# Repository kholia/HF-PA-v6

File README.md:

### HF-PA-v6

RF "Lego" blocks.

The idea behind this work is to build radio-things (TM) in stages which
connect to each other.

Note: This `HF-PA-v6` is like https://github.com/kholia/HF-PA-v5 which has been
broken out in stages. This makes the designing, and debugging processes much
easier.

#### Results

October-2022 UPDATE: The PCB manufactured by JLCPCB was successfully validated.
We could get 5W+ with IRF510 @ 20v drain @ 28 MHz. Output at 14 MHz can be more
than 10W easily too.

PCB bug (in `HF-PA-Combined` version): Please cut the positive trace going
between C15 and JP2 to enable dynamic PA voltage control using PTT. This bug
is fixed in `HF-PA-Combined-v2` version for future production.

NOTE: See https://github.com/kholia/HF-PA-v6/tree/master/HF-PA-Combined for the
schematics, design files, and a PCB render screenshot.

IRF510 @ 14 MHz -> 20v @ drain. RF output > 7.5W. No LPF. Clean'ish looking
output. No oscillations. BS170 @ 5.5v. DC bias set high for max'ish "Idq".

IRF510 @ 21 MHz -> 15v @ drain. 12.75W DC input. RF output > 3W. No LPF.
Clean'ish looking output. No oscillations. BS170 @ 5.5v. DC bias set high for
max'ish "Idq". Almost 4W can be achieved with max "Idq".

IRF510 @ 28 MHz -> 14v @ drain. 9W DC input. RF output > 2W (on meter). No LPF.
Clean'ish looking output. No oscillations. BS170 @ 5.5v. DC bias set high for
max'ish "Idq".

IRF510 @ 28 MHz -> 17v @ drain. RF output > 2.25W (on scope), 3.5W on RF power
meter. No LPF. Clean'ish looking output. No oscillations. BS170 @ 6v. DC bias
set high for max "Idq" @ 4.2v roughly.

Note: We can even use 30v (and higher+) drain voltages (PA voltages) with
IRF510 - with much more care though!

Even 3W can get worldwide DX contacts when propagation is playing along ;)

7W (or less) of HF RF power offers global communications coverage when
propagation is good:

#### BOM Notes

See https://github.com/kholia/HF-PA-v5 for the BOM and BOM sources.

- https://github.com/kholia/HF-PA-v5#pa-bom

- https://github.com/kholia/HF-PA-v5#bom--equipment-sources

#### Build Notes

L1 can be a simple choke (FT37-43 25 turns of 27 to 29 SWG wire).

L2 needs to be a bifilar transformer on FT50-43 core (10 turns with 24/25/26
SWG wire).

#### Notes

[BS170 Driver Performance](./BS170-Driver-Performance.txt)

As Vds is increased, the Vgs needs to be increased too - see the following
graph.

If the gate DC bias is too less, the MOSFET will not turn on properly, and will
generate a lot of distortion - one prominent distorted waveform will be at
half-the-operating frequency!

When operating at max "Idq" (for best linearity), the power to the IRF510
should be PTT controlled - otherwise too much (battery) power will turn to heat
instead of RF!

#### Special Notes

While IRF510 can get destroyed due to oscillations, in my case it has been a
failed 7805 (or 78L05) regulator which ultimately causes cascading failures.

A 7805 regulator can fail in fail-short mode, where `Vout == Vin`! This changes
the bias of the driver stage (BS170), and it goes in full conduction
immediately without any RF input because Vgs(th) is exceeded quite easily.
This causes further failures in the PA system!

My 7805s (and 78L05s) of dubious origin were failing (Vout shorted to Vin!)
around 20v to 24v. Here is what `bd139` (from https://www.eevblog.com/forum/)
has to say on this topic,

```
None of the voltage regulators work properly above about 20V if you want 5V
out. If you need to drop more, add a preregulator.

I found this out the hard way as well dropping 28V to 5V DC for logic in an RF
PA driver. Currently waiting for a board spin. I only needed 50mA and didn't
want RF noise so I went with a simple MOSFET/zener/resistor preregulator to
drop it down to 18Vish. Because the current requirements are relatively low I
don't need to heatsink either then as the load is spread evenly across both
MOSFET and 7805.

Also if you value the circuit it's driving, stick a 5W 5.6V zener across the
regulator output. That will smoke the prereg / regulator not the load!
```

Thank you `bd139`!

#### PCB Renderings

#### Joining In

Are you interested in such projects, and spam-free technical discussions?

If yes, you might be interested in joining [the 'HAMBREWERS' Telegram group](https://t.me/+TwzGyKGe8_QI_B3y).

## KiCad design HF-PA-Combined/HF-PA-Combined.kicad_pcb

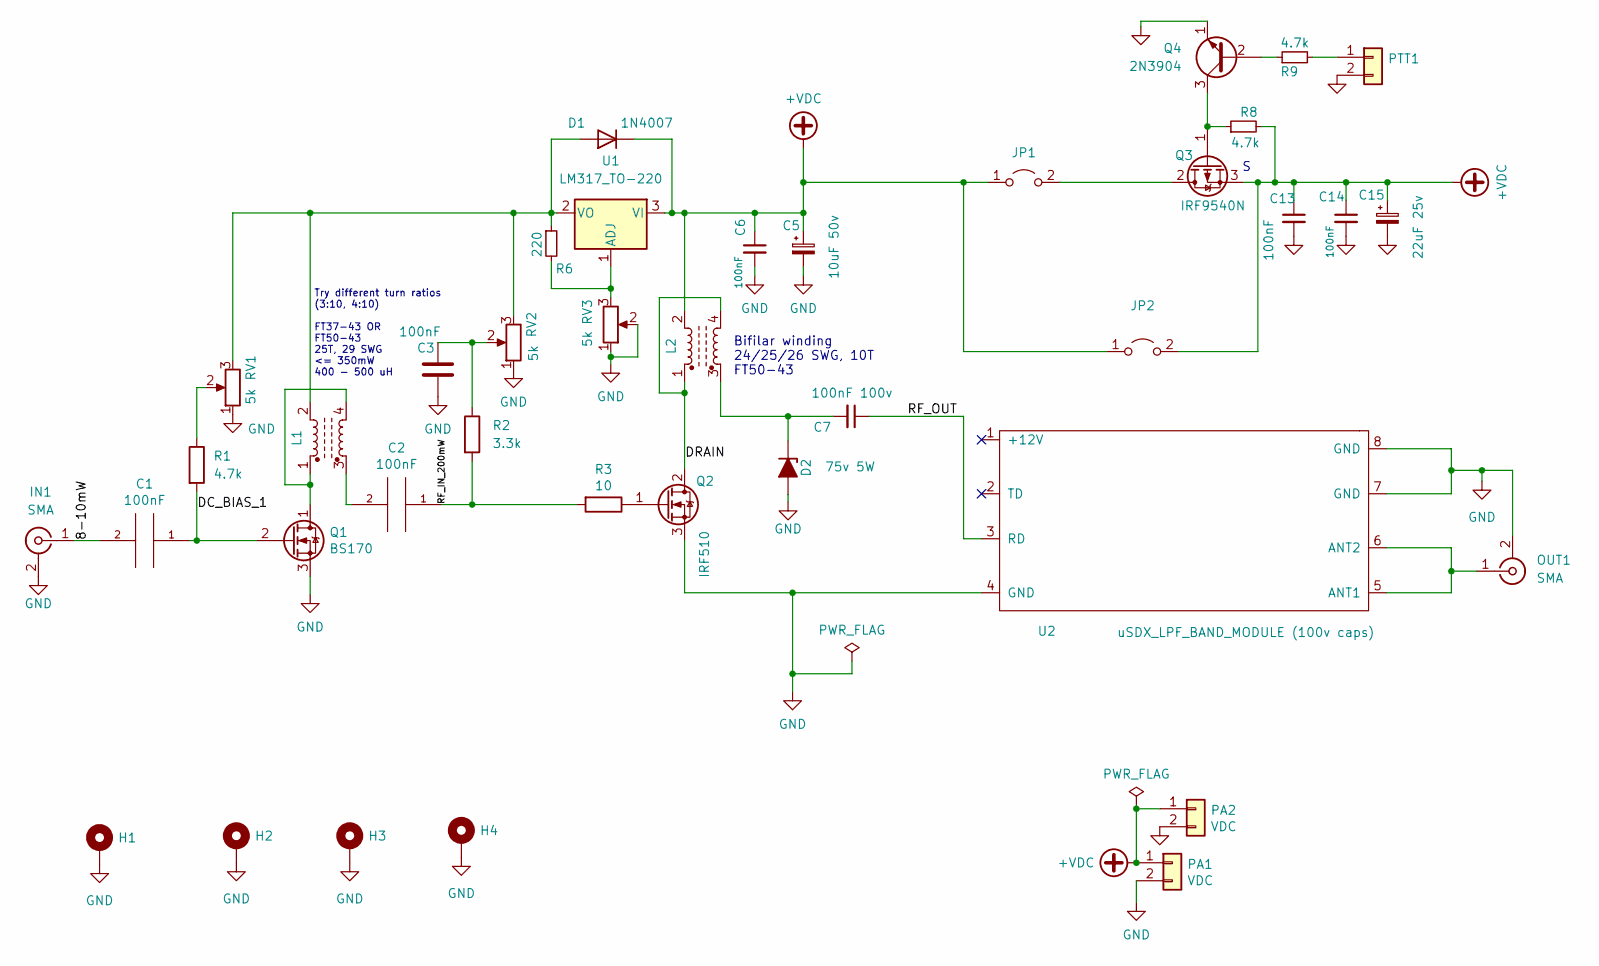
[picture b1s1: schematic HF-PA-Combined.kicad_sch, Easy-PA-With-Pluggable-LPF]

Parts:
C1, C2, C3, C6, C13, C14: 100nF; C_1206_3216Metric_Pad1.33x1.80mm_HandSolder
C5: 10uF 50v; C_1206_3216Metric_Pad1.33x1.80mm_HandSolder
C7: 100nF 100v; C_1206_3216Metric_Pad1.33x1.80mm_HandSolder
C15: 22uF 25v; CP_Radial_D5.0mm_P2.50mm
D1: 1N4007; D_DO-41_SOD81_P2.54mm_Vertical_KathodeUp
D2: 75v 5W; D_DO-201_P5.08mm_Vertical_AnodeUp
H1, H2, H3, H4: MountingHole_Pad; MountingHole_3.2mm_M3_ISO7380_Pad
IN1: SMA; SMA_Amphenol_901-144_Vertical
JP1, JP2: Jumper_2_Open; PinHeader_1x02_P2.54mm_Vertical
L1, L2: L_Ferrite_Coupled; FT50-43 Transformer
OUT1: SMA; SMA_Amphenol_901-144_Vertical
PA1, PA2: VDC; PinHeader_1x02_P2.54mm_Vertical
PTT1: PTT; PinHeader_1x02_P2.54mm_Vertical
Q1: BS170; PinSocket_1x03_P2.54mm_Vertical
Q2: IRF510; TO-220-3_Vertical
Q3: IRF9540N; TO-220-3_Vertical
Q4: 2N3904; PinSocket_1x03_P2.54mm_Vertical
R1, R8, R9: 4.7k; R_1206_3216Metric_Pad1.30x1.75mm_HandSolder
R2: 3.3k; R_1206_3216Metric_Pad1.30x1.75mm_HandSolder
R3: 10; R_1206_3216Metric_Pad1.30x1.75mm_HandSolder
R6: 220; R_1206_3216Metric_Pad1.30x1.75mm_HandSolder
RV1, RV2, RV3: 5k; Potentiometer_Runtron_RM-065_Vertical
U1: LM317_TO-220; TO-220-3_Vertical
U2: uSDX_LPF_BAND_MODULE (100v caps); uSDX_LPF_Band_Module

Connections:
+VDC: C5.1, C6.1, C13.1, C14.1, C15.1, D1.1 (K), JP1.1 (A), JP2.1 (A), JP2.2 (B), L2.2, PA1.1, PA2.1, Q3.3 (S), R8.2, U1.3 (VI)
/8-10mW: C1.2, IN1.1 (In)
/DC_BIAS_1: C1.1, Q1.2 (G), R1.2
/DRAIN: L2.1, L2.4, Q2.2 (D)
/RF_IN_200mW: C2.1, R2.2, R3.2
/RF_OUT: C7.1, U2.3 (RD)
GND: C3.2, C5.2, C6.2, C13.2, C14.2, C15.2, D2.2 (A), H1.1, H2.1, H3.1, H4.1, IN1.2 (Ext), OUT1.2 (Ext), PA1.2, PA2.2, PTT1.2, Q1.3 (S), Q2.3 (S), Q4.1 (E), RV1.1, RV2.1, RV3.1, RV3.2, U2.4 (GND), U2.7 (GND), U2.8 (GND)
unnamed: C3.1, R2.1, RV2.2
unnamed: C7.2, D2.1 (K), L2.3
unnamed: D1.2 (A), L1.2, R6.1, RV1.3, RV2.3, U1.2 (VO)
unnamed: JP1.2 (B), Q3.2 (D)
unnamed: C2.2, L1.3
unnamed: OUT1.1 (In), U2.5 (ANT1), U2.6 (ANT2)
unnamed: PTT1.1, R9.2
unnamed: L1.1, L1.4, Q1.1 (D)
unnamed: Q2.1 (G), R3.1
unnamed: Q3.1 (G), Q4.3 (C), R8.1
unnamed: Q4.2 (B), R9.1
unnamed: R1.1, RV1.2
unnamed: R6.2, RV3.3, U1.1 (ADJ)

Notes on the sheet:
Bifilar winding 24/25/26 SWG, 10T FT50-43
Try different turn ratios (3:10, 4:10) FT37-43 OR FT50-43 25T, 29 SWG <= 350mW 400 - 500 uH

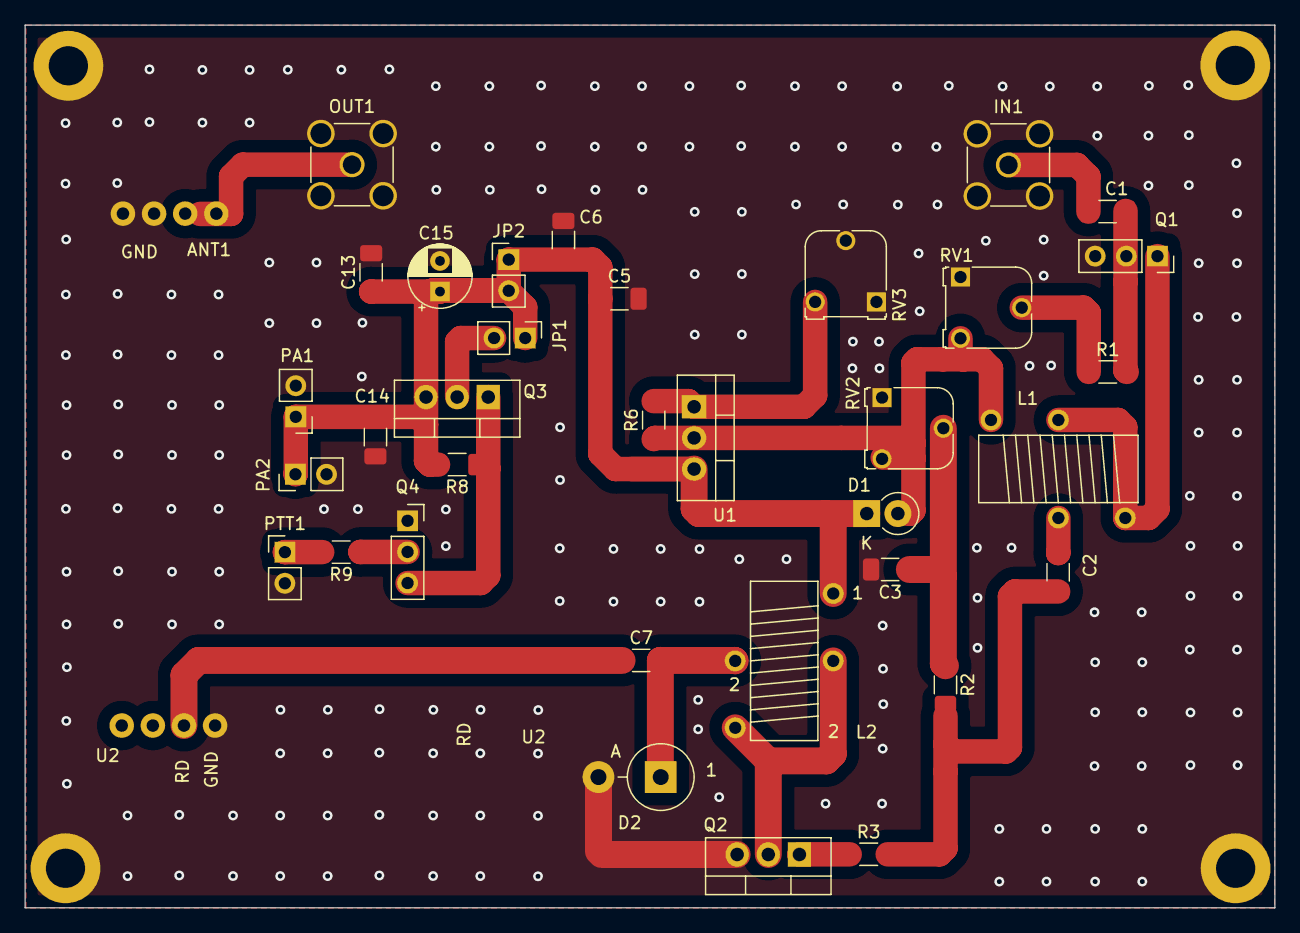
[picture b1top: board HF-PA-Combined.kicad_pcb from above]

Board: 2 copper layers, 102.0 x 72.0 mm, 39 parts (0 on the bottom side), 20 nets.

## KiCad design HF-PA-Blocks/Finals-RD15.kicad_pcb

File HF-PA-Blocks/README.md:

The `Finals-RD15.kicad_pcb` is oversized on purpose for two reasons:

- To avoid the tedious job of cutting the larger 3x2 PCB into a smaller size.

- To save etchant by putting a copper pour over the larger area.

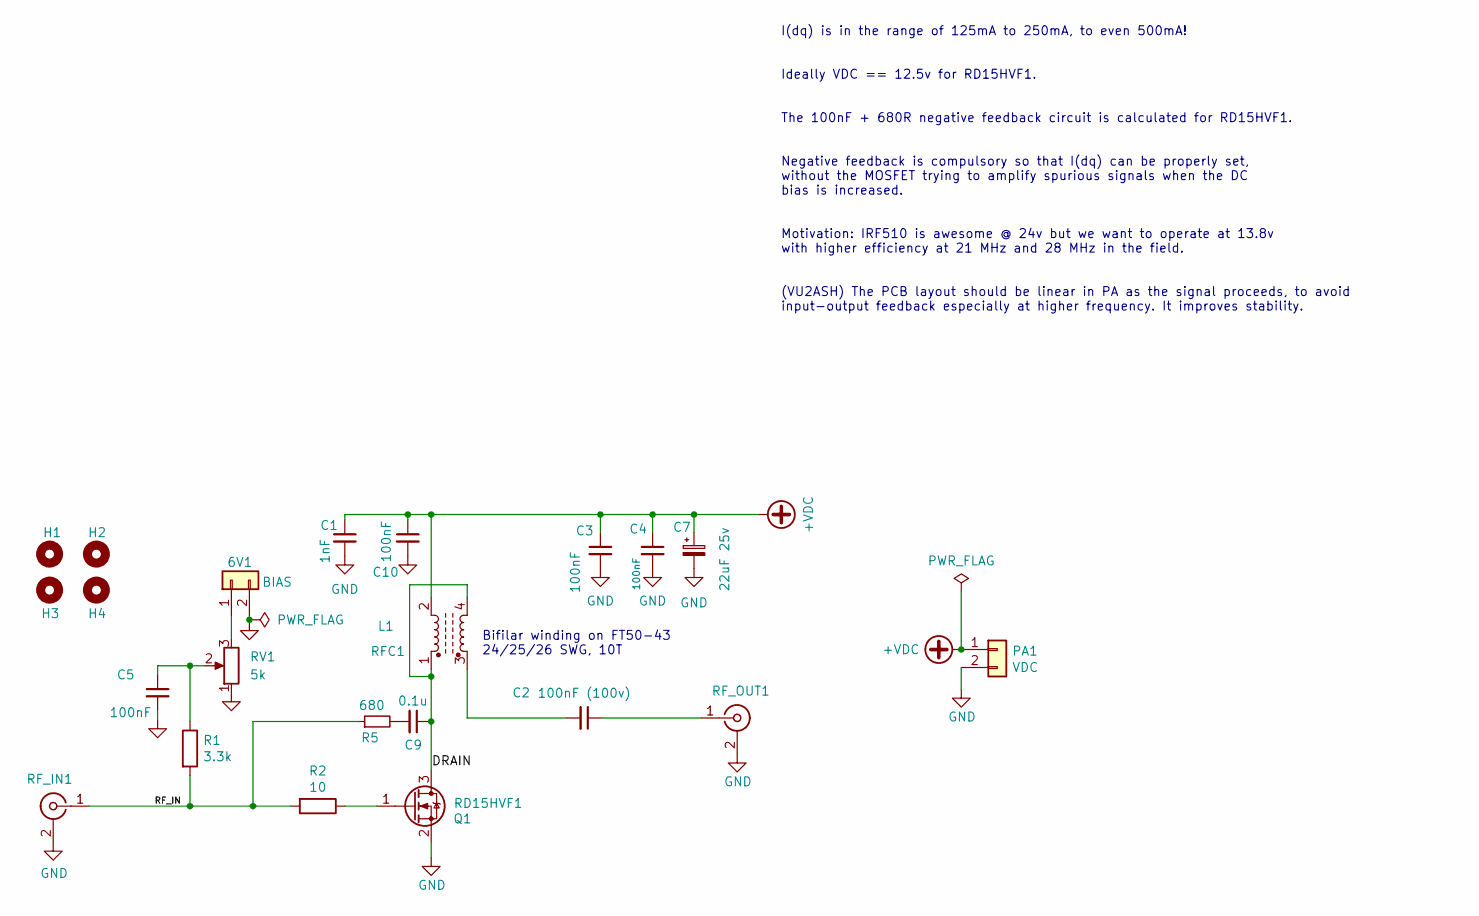
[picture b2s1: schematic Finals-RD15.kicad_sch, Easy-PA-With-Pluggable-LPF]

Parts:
6V1: BIAS; PinHeader_1x02_P2.54mm_Vertical
C1: 1nF; C_1206_3216Metric_Pad1.33x1.80mm_HandSolder
C2: 100nF (100v); C_1206_3216Metric_Pad1.33x1.80mm_HandSolder
C3, C4, C5, C10: 100nF; C_1206_3216Metric_Pad1.33x1.80mm_HandSolder
C7: 22uF 25v; CP_Radial_D5.0mm_P2.50mm
C9: 0.1u; C_1206_3216Metric_Pad1.33x1.80mm_HandSolder
H1, H2, H3, H4: MountingHole; MountingHole_2.2mm_M2
L1: RFC1; FT50-43 Transformer
PA1: VDC; PinHeader_1x02_P2.54mm_Vertical
Q1: RD15HVF1; TO-220-3_Vertical
R1: 3.3k; R_1206_3216Metric_Pad1.30x1.75mm_HandSolder
R2: 10; R_1206_3216Metric_Pad1.30x1.75mm_HandSolder
R5: 680; R_1206_3216Metric_Pad1.30x1.75mm_HandSolder
RF_IN1: Conn_Coaxial; SMA_Amphenol_901-144_Vertical
RF_OUT1: Conn_Coaxial; SMA_Amphenol_901-144_Vertical
RV1: 5k; Potentiometer_Runtron_RM-065_Vertical

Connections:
+VDC: C1.1, C3.1, C4.1, C7.1, C10.1, L1.2, PA1.1
/DRAIN: C9.1, L1.1, L1.4, Q1.3 (D)
/RF_IN: R1.2, R2.2, R5.1, RF_IN1.1 (In)
GND: 6V1.2, C1.2, C3.2, C4.2, C5.2, C7.2, C10.2, PA1.2, Q1.2 (S), RF_IN1.2 (Ext), RF_OUT1.2 (Ext), RV1.1
unnamed: 6V1.1, RV1.3
unnamed: C2.1, RF_OUT1.1 (In)
unnamed: C2.2, L1.3
unnamed: C5.1, R1.1, RV1.2
unnamed: C9.2, R5.2
unnamed: Q1.1 (G), R2.1

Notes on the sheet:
I(dq) is in the range of 125mA to 250mA, to even 500mA! Ideally VDC == 12.5v for RD15HVF1. The 100nF + 680R negative feedback circuit is calculated for RD15HVF1. Negative feedback is compulsory so that I(dq) can be properly set, without the MOSFET trying to amplify spurious signals when the DC bias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
Bifilar winding on FT50-43 24/25/26 SWG, 10T

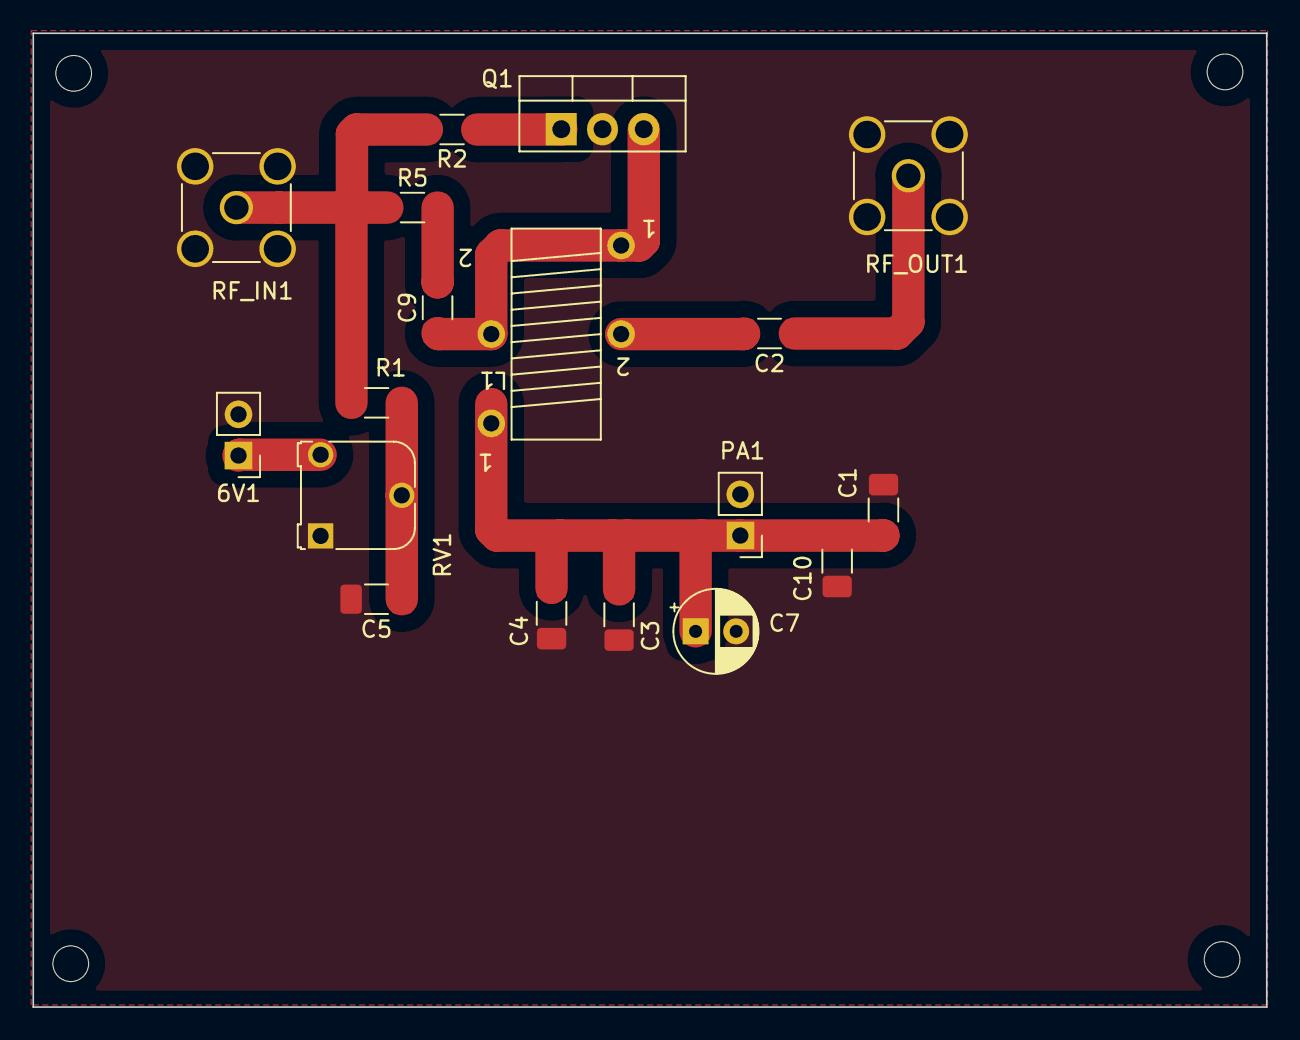
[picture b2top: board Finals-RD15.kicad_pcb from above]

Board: 2 copper layers, 76.0 x 60.0 mm, 22 parts (0 on the bottom side), 10 nets.

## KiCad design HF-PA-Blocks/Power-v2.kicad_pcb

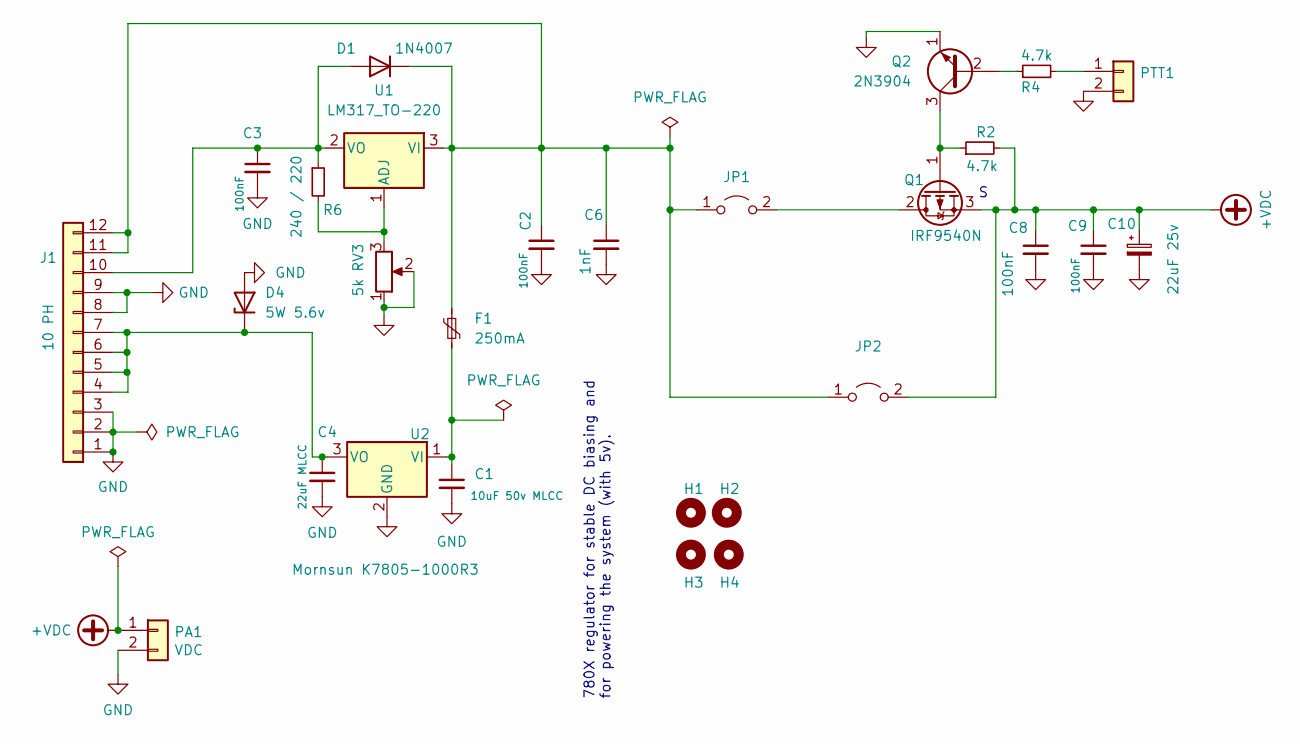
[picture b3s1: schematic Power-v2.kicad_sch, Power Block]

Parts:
C1: 10uF 50v MLCC; C_1206_3216Metric_Pad1.33x1.80mm_HandSolder
C2, C3, C8, C9: 100nF; C_1206_3216Metric_Pad1.33x1.80mm_HandSolder
C4: 22uF MLCC; C_1206_3216Metric_Pad1.33x1.80mm_HandSolder
C6: 1nF; C_1206_3216Metric_Pad1.33x1.80mm_HandSolder
C10: 22uF 25v; CP_Radial_D5.0mm_P2.50mm
D1: 1N4007; D_SMA_Handsoldering
D4: 5W 5.6v; D_DO-15_P5.08mm_Vertical_KathodeUp
F1: 250mA; C_Disc_D5.0mm_W2.5mm_P5.00mm
H1, H2, H3, H4: MountingHole; MountingHole_2.2mm_M2
J1: 10 PH; PinHeader_1x12_P2.54mm_Vertical
JP1, JP2: Jumper_2_Open; PinHeader_1x02_P2.54mm_Vertical
PA1: VDC; PinHeader_1x02_P2.54mm_Vertical
PTT1: PTT; PinHeader_1x02_P2.54mm_Vertical
Q1: IRF9540N; TO-220-3_Vertical
Q2: 2N3904; PinSocket_1x03_P2.54mm_Vertical
R2, R4: 4.7k; R_1206_3216Metric_Pad1.30x1.75mm_HandSolder
R6: 240 / 220; R_1206_3216Metric_Pad1.30x1.75mm_HandSolder
RV3: 5k; Potentiometer_Runtron_RM-065_Vertical
U1: LM317_TO-220; TO-220-3_Vertical
U2: Mornsun K7805-1000R3; TO-220-3_Vertical

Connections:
+VDC: C8.1, C9.1, C10.1, JP2.2 (B), PA1.1, Q1.3 (S), R2.2
GND: C1.2, C2.2, C3.2, C4.2, C6.2, C8.2, C9.2, C10.2, D4.2 (A), J1.1, J1.2, J1.3, J1.8, J1.9, PA1.2, PTT1.2, Q2.1 (E), RV3.1, RV3.2, U2.2 (GND)
unnamed: C1.1, F1.2, U2.1 (VI)
unnamed: C2.1, C6.1, D1.1 (K), F1.1, J1.11, J1.12, JP1.1 (A), JP2.1 (A), U1.3 (VI)
unnamed: C3.1, D1.2 (A), J1.10, R6.1, U1.2 (VO)
unnamed: C4.1, D4.1 (K), J1.4, J1.5, J1.6, J1.7, U2.3 (VO)
unnamed: JP1.2 (B), Q1.2 (D)
unnamed: PTT1.1, R4.2
unnamed: Q1.1 (G), Q2.3 (C), R2.1
unnamed: Q2.2 (B), R4.1
unnamed: R6.2, RV3.3, U1.1 (ADJ)

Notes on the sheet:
780X regulator for stable DC biasing and for powering the system (with 5v).

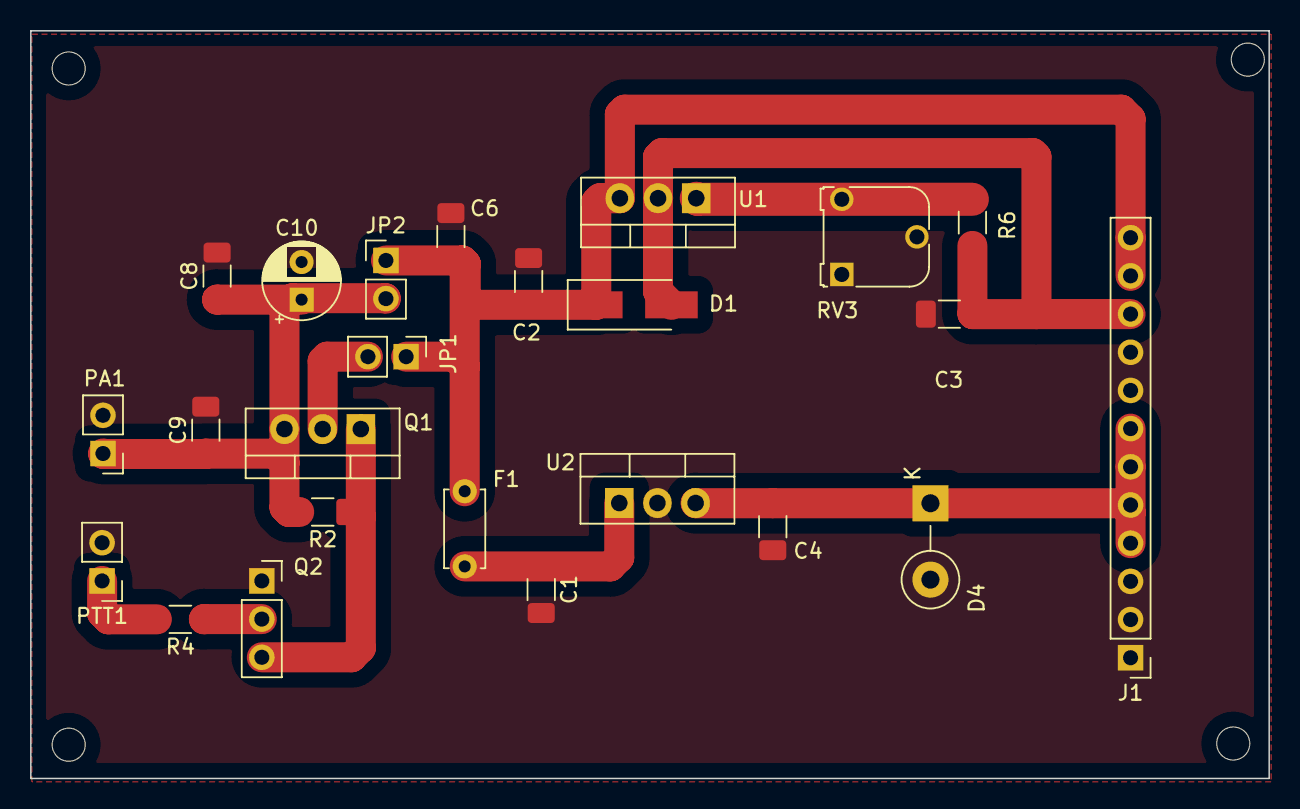
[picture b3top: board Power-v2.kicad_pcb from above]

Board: 2 copper layers, 82.4 x 49.7 mm, 28 parts (0 on the bottom side), 11 nets.

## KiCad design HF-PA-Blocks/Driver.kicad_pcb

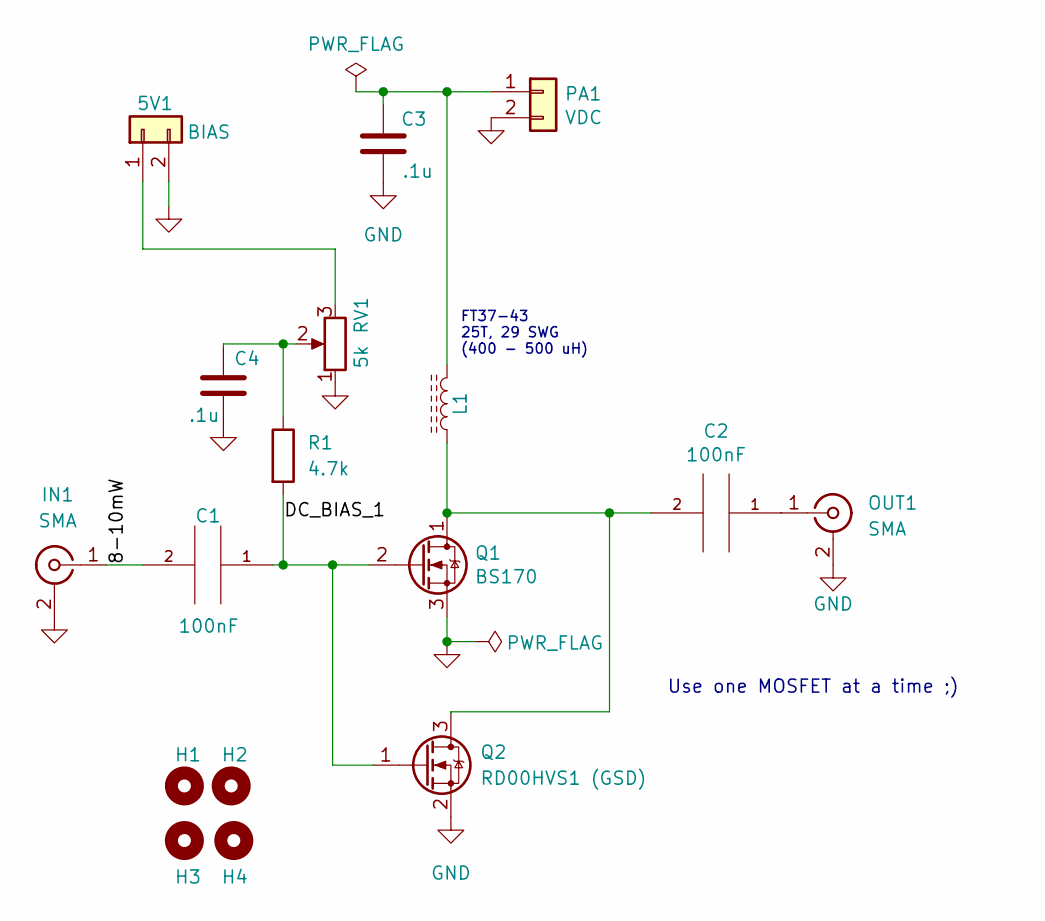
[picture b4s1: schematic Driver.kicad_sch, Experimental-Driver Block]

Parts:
5V1: BIAS; PinHeader_1x02_P2.54mm_Vertical
C1, C2: 100nF; C_1206_3216Metric_Pad1.33x1.80mm_HandSolder
C3, C4: .1u; C_1206_3216Metric_Pad1.33x1.80mm_HandSolder
H1, H2, H3, H4: MountingHole; MountingHole_2.2mm_M2
IN1: SMA; SMA_Amphenol_901-144_Vertical
L1: L_Ferrite; L_Toroid_Vertical_L10.0mm_W5.0mm_P5.08mm
OUT1: SMA; SMA_Amphenol_901-144_Vertical
PA1: VDC; PinHeader_1x02_P2.54mm_Vertical
Q1: BS170; PinSocket_1x03_P2.54mm_Vertical
Q2: RD00HVS1 (GSD); PinSocket_1x03_P2.54mm_Vertical
R1: 4.7k; R_1206_3216Metric_Pad1.30x1.75mm_HandSolder
RV1: 5k; Potentiometer_Runtron_RM-065_Vertical

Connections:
/8-10mW: C1.2, IN1.1 (In)
/DC_BIAS_1: C1.1, Q1.2 (G), Q2.1 (G), R1.2
GND: 5V1.2, C3.2, C4.2, IN1.2 (Ext), OUT1.2 (Ext), PA1.2, Q1.3 (S), Q2.2 (S), RV1.1
unnamed: 5V1.1, RV1.3
unnamed: C2.1, OUT1.1 (In)
unnamed: C2.2, L1.1, Q1.1 (D), Q2.3 (D)
unnamed: C3.1, L1.2, PA1.1
unnamed: C4.1, R1.1, RV1.2

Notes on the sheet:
Use one MOSFET at a time ;)
FT37-43 25T, 29 SWG (400 - 500 uH)

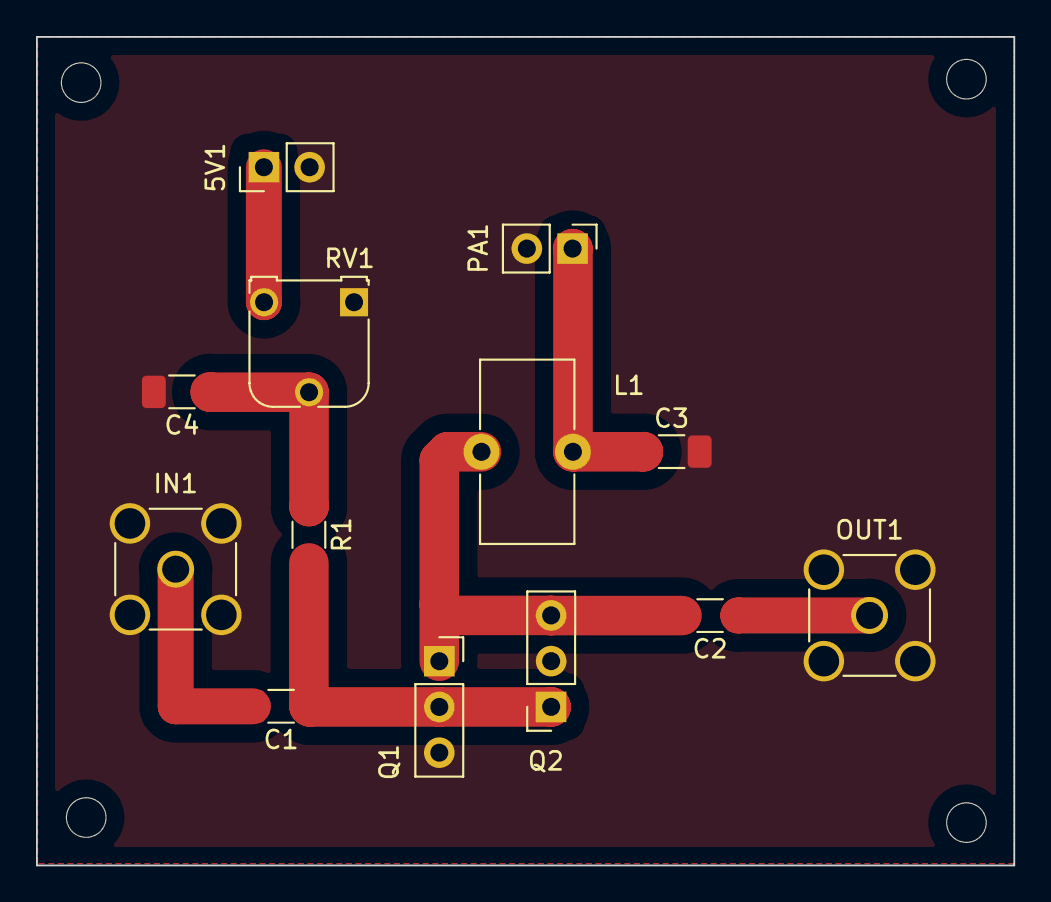
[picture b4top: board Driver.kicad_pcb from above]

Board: 2 copper layers, 54.3 x 46.0 mm, 17 parts (0 on the bottom side), 8 nets.

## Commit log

2022-05-05 Initial PoC
